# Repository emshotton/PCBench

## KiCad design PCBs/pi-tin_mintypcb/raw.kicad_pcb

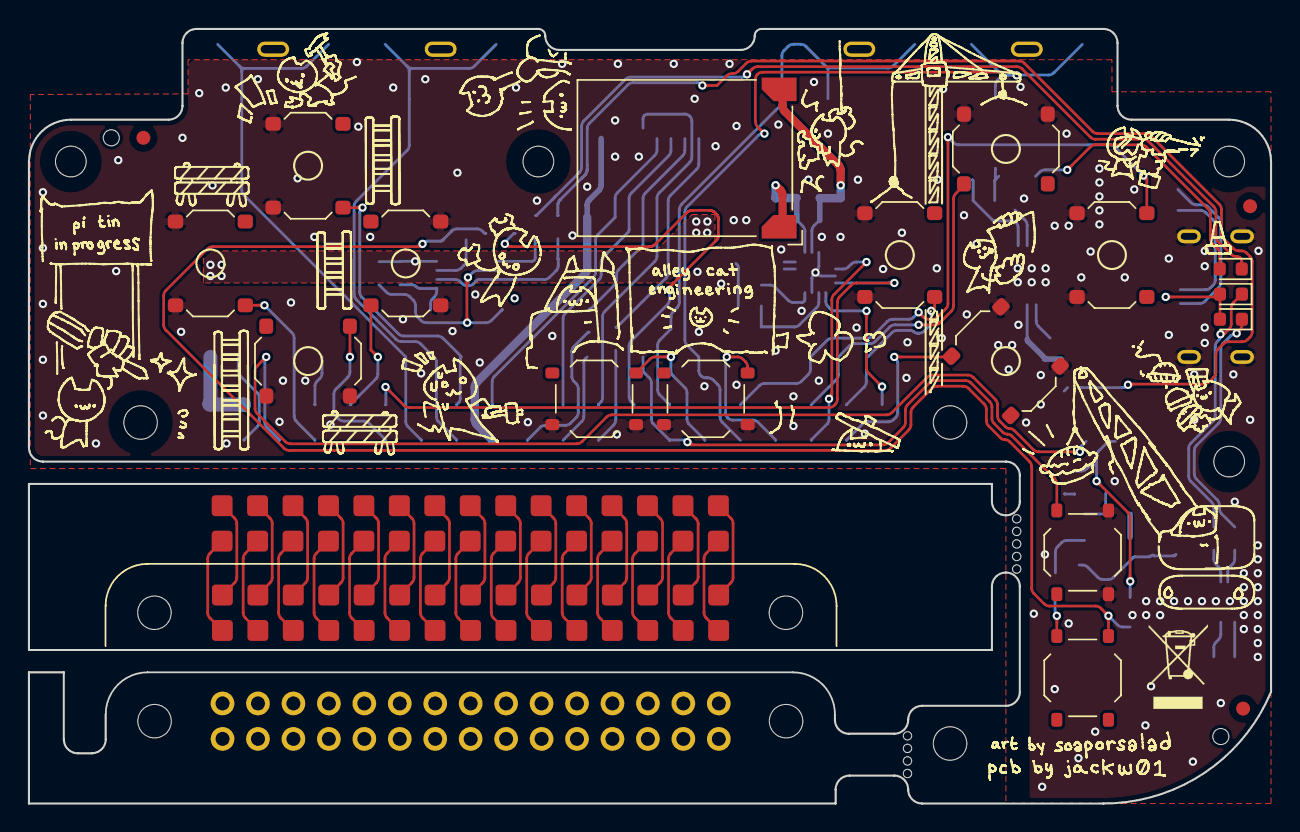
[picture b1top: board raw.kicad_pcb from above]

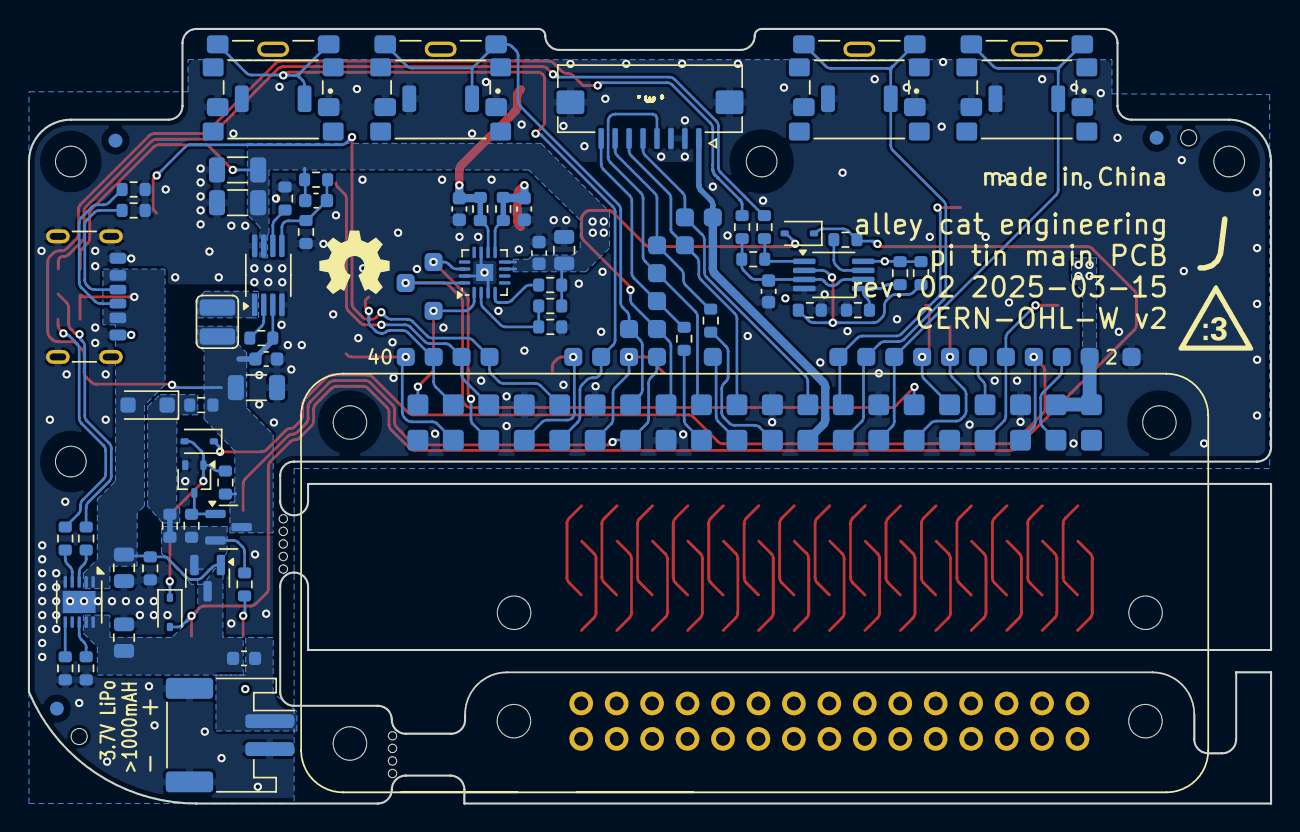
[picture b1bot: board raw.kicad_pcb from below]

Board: 2 copper layers, 89.0 x 55.5 mm, 126 parts (99 on the bottom side), 97 nets.

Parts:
A101: Raspberry Pi Zero 2 W; RASPBERRYPI-ZERO_RPI-ZERO_pi_tin
C101, C102, C105: 22u; C_1206_3216Metric
C103, C104, C108: 10u; C_0805_2012Metric
C106, C109, C112: 0.1u; C_0603_1608Metric
C107: ?; C_0603_1608Metric
C110, C111: 220p; C_0603_1608Metric
D101: DSK110; D_SOD-123F
D102: orange; LED_0603_1608Metric
D103: LED; LED_0603_1608Metric
D104: green; LED_0603_1608Metric
D105, D106, D107: BAT54; D_SOD-323
F101: 1A; Fuse_0603_1608Metric
FB103, FB104: 120R@100MHz; R_0603_1608Metric_Bridged
FID101, FID102, FID103, FID104, FID105, FID106: Fiducial_1mm_Mask2mm
H101, H103, H105, H106: MountingHole; MountingHole_2.2mm_M2_Mask_tight
H102, H104: ToolingHole; JLC_tooling_hole
J101: USB C 6 pin; USB_C_Receptacle_6PIN_generic
J102: S2B-PH-SM4-TB; JST_PH_S2B-PH-SM4-TB_1x02-1MP_P2.00mm_Horizontal
J103: FPC09-Q1.0-8; XYECONN_FPC09-Q1.0-8AH2.0
J106: Conn_02x15_Odd_Even; pi_tin_pi_simulator
J107: Conn_02x15_Odd_Even; pi_tin_pi_simulator_lands
J108: Conn_02x15_Odd_Even; pi_tin_pi_simulator_tp
L101: 2.2u; L_3225DFN
LS101: CMS-151125-076S-67; Speaker_CUI_CMR-1206S-67
Q101, Q102: 3415; SOT-23
Q103: BSS138; SOT-323_SC-70
R101, R111, R121: 10k; R_0603_1608Metric
R102: 0; R_0603_1608Metric_Bridged
R103: 0; R_0603_1608Metric
R104, R128: 22; R_0603_1608Metric
R105, R109, R110, R114, R120: 1.69k; R_0603_1608Metric
R106, R112, R113, R115, R122, R125, R127, R129: 100k; R_0603_1608Metric
R107: 49.9k; R_0603_1608Metric
R108, R126: 750k; R_0603_1608Metric
R116, R117, R123, R124: 5.1k; R_0603_1608Metric
R118: ?; R_0603_1608Metric
R119: 68k; R_0603_1608Metric
SW101, SW103, SW105, SW115: SKQGABE010; SW_PTS526
SW102, SW104, SW106, SW108, SW110, SW112, SW114, SW116: SKRRAAE010; SW_SKRR
SW107, SW109, SW111, SW113: see note 1; SW_TL3336AF160Q_or_PTS645_paste1
TP101, TP102, TP103, TP104, TP105, TP106, TP107, TP108, TP109, TP110, TP111, TP112, TP113, TP114, TP115, TP116, TP117, TP118, TP119, TP120, TP121, TP122, TP123, TP124, TP125, TP126, TP127, TP128, TP129, TP130, TP131: TestPoint_Small; TestPoint_Pad_D1.5mm
U101: LMV393; MSOP-8_3x3mm_P0.65mm
U102: MCP73833T-FCI/MF; DFN-10-1EP_3x3mm_P0.5mm_EP1.58x2.35mm
U103: PAM2401SCADJ; MSOP-8_3x3mm_P0.65mm
U104: MAX98357A; TQFN-16-1EP_3x3mm_P0.5mm_EP1.23x1.23mm

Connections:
+3.3V: A101.17 (3V3[2]), J103.1, TP113.1
+5V: A101.2 (5V[1]), A101.4 (5V[2]), C101.1, C102.1, C107.1, C108.1, C109.1, D102.2 (A), R107.2, R108.1, R119.2, R125.1, R126.1, TP102.1, U101.8 (V+), U103.7 (OUT), U104.7 (VDD), U104.8 (VDD)
+BATT: C105.1, C106.1, L101.1, Q102.3 (D), R103.1, R111.2, R112.2, R123.1, U103.3 (VIN)
/A: A101.32 (GPIO12), SW110.1, TP125.1
/B: A101.37 (GPIO26), SW112.1, TP129.1
/BATT_SW_EN: D106.1 (K), D107.2 (A), Q103.1 (G), R111.1
/DOWN: A101.11 (GPIO17/GEN0), SW104.1, TP108.1
/D/C: A101.22 (GEN/6GPIO25), J103.6, TP117.1
/I2S_BCLK: A101.12 (GPIO18), TP109.1, U104.16 (BCLK)
/I2S_DIN: A101.40 (GPIO21), TP131.1, U104.1 (DIN)
/I2S_LRCLK: A101.35 (GPIO19), TP127.1, U104.14 (LRCLK)
/L1: A101.31 (GPIO6), SW107.1, TP124.1
/L2: A101.28 (ID_SC), SW111.1, TP122.1
/LEFT: A101.7 (GPIO4/GPCKL0), SW106.1, TP104.1
/LOW_BATT: R124.1, U101.7
/PS_EN: R112.1, U103.2 (EN)
/R1: A101.13 (GPIO27/GEN2), SW109.1, TP110.1
/R2: A101.15 (GPIO22/GEN3), SW113.1, TP111.1
/RIGHT: A101.10 (RXD0/GPIO15), SW108.1, TP107.1
/RST: A101.18 (GEN5/GPIO24), J103.5, TP114.1
/SELECT: A101.29 (GPIO5), SW105.1, TP123.1
/SHUTDOWN_PI: A101.26 (~CE1/~GPIO7), D105.2 (A), TP120.1
/SHUTDOWN_PS: A101.5 (GPIO3/SCL), D107.1 (K), TP103.1
/SPECIAL1: A101.27 (ID_SD), SW115.1, TP121.1
/SPI_CS: A101.24 (~CE0/GPIO8), J103.4, TP119.1
/SPI_MOSI: J103.7, R104.1, TP115.1
/SPI_SCK: J103.8, R128.1, TP118.1
/START: A101.33 (GPIO13), SW103.1, TP126.1
/UP: A101.16 (GEN4/GPIO23), SW102.1, TP112.1
/X: A101.36 (GPIO16), SW114.1, TP128.1
/Y: A101.38 (GPIO20), SW116.1, TP130.1
/_SPI_MOSI: A101.19 (GPIO10/MOSI), R104.2
/_SPI_SCK: A101.23 (GPIO11/SCLK), R128.2
GND: A101.6 (GND[8]), A101.9 (GND[1]), A101.14 (GND[4]), A101.20 (GND[5]), A101.25 (GND[2]), A101.30 (GND[6]), A101.34 (GND[7]), A101.39 (GND[3]), C101.2, C102.2, C103.2, C104.2, C105.2, C106.2, C108.2, C109.2, C110.2, C111.2, C112.2, J101.A12 (GND), J101.B12 (GND), J101.S1 (SHIELD), J102.2, J102.MP (MountPin), J103.2, J103.3, J103.MP (MountPin), Q103.2 (S), R101.1, R113.1, R115.2, R116.1, R117.1, R118.2, R120.1, R121.1, R122.1, R127.2, SW102.2, SW103.2, SW104.2, SW105.2, SW106.2, SW107.2, SW108.2, SW109.2, SW110.2, SW111.2, SW112.2, SW113.2, SW114.2, SW115.2, SW116.2, TP106.1, U101.4 (V-), U102.5 (V_{SS}), U102.11 (EP), U103.4 (AGND), U103.8 (PGND), U104.3 (GND), U104.11 (GND), U104.15 (GND), U104.17 (PAD)
unnamed: A101.3 (GPIO2/SDA), TP101.1
unnamed: A101.21 (GPIO9/MISO), TP116.1
unnamed: A101.8 (TXD0/GPIO14), TP105.1
unnamed: C110.1, FB103.2, LS101.1
unnamed: C111.1, FB104.2, LS101.2
unnamed: D101.1 (K), R102.2, R103.2
unnamed: D102.1 (K), R105.2
unnamed: D103.1 (K), R109.2
unnamed: D104.1 (K), R110.2
unnamed: D105.1 (K), D106.2 (A), R124.2, SW101.1
unnamed: J101.A5 (CC1), R117.2
unnamed: J101.B5 (CC2), R116.2
unnamed: F101.2, J102.1
unnamed: J107.1, J108.1
unnamed: J107.2, J108.2
unnamed: J107.3, J108.3
unnamed: J107.4, J108.4
unnamed: J107.5, J108.5
unnamed: J107.6, J108.6
unnamed: J107.7, J108.7
unnamed: J107.8, J108.8
unnamed: J107.9, J108.9
unnamed: J107.10, J108.10
unnamed: J107.11, J108.11
unnamed: J107.12, J108.12
unnamed: J107.13, J108.13
unnamed: J107.14, J108.14
unnamed: J107.15, J108.15
unnamed: J107.16, J108.16
unnamed: J107.17, J108.17
unnamed: J107.18, J108.18
unnamed: J107.19, J108.19
unnamed: J107.20, J108.20
unnamed: J107.21, J108.21
unnamed: J107.22, J108.22
unnamed: J107.23, J108.23
unnamed: J107.24, J108.24
unnamed: J107.25, J108.25
unnamed: J107.26, J108.26
unnamed: J107.27, J108.27
unnamed: J107.28, J108.28
unnamed: J107.29, J108.29
unnamed: J107.30, J108.30
unnamed: C104.1, F101.1, Q101.3 (D), U102.9 (V_{BAT}), U102.10 (V_{BAT})
unnamed: Q101.2 (S), Q102.2 (S), R102.1, R106.2, R114.2
unnamed: Q102.1 (G), Q103.3 (D), R106.1
unnamed: R105.1, R129.2, U101.1
unnamed: R114.1, SW101.2
unnamed: C112.1, R123.2, R129.1, U101.3 (+), U101.6 (-)
unnamed: R107.1, R113.2, U101.2 (-)
unnamed: R119.1, R122.2, U101.5 (+)
unnamed: R120.2, U102.6 (PROG)
unnamed: R110.1, U102.3 (STAT1)
unnamed: R109.1, U102.4 (STAT2)
unnamed: R121.2, U102.8 (THERM)
unnamed: C107.2, R108.2, R115.1, U103.5 (FB)
unnamed: L101.2, U103.1 (LX)
unnamed: R118.1, U103.6 (RSET)
unnamed: R125.2, R127.1, U104.2 (GAIN_SLOT)
unnamed: FB104.1, U104.10 (OUTN)
unnamed: FB103.1, U104.9 (OUTP)
unnamed: R126.2, U104.4 (~SD_MODE)
VBUS: C103.1, D101.2 (A), D103.2 (A), D104.2 (A), J101.A9 (VBUS), J101.B9 (VBUS), Q101.1 (G), R101.2, U102.1 (V_{DD}), U102.2 (V_{DD})

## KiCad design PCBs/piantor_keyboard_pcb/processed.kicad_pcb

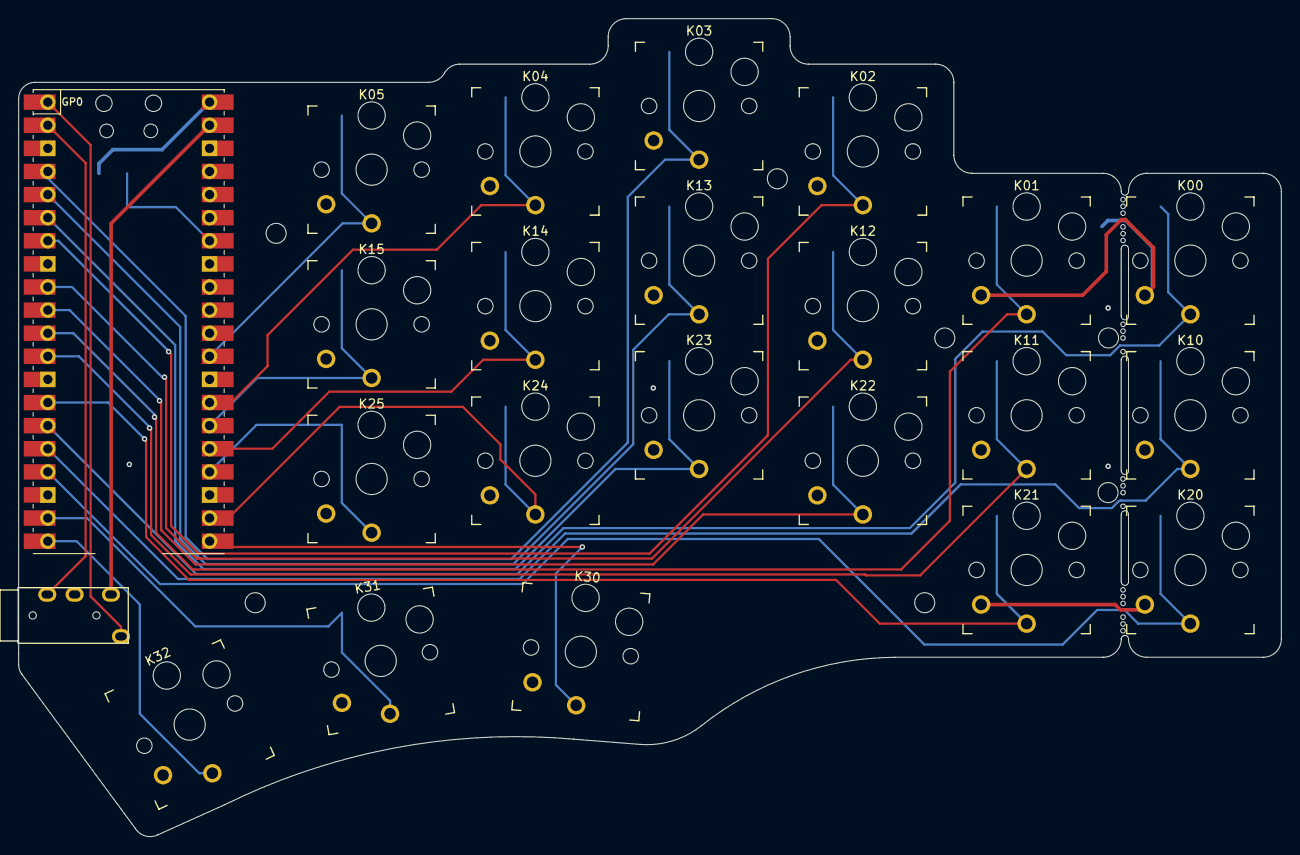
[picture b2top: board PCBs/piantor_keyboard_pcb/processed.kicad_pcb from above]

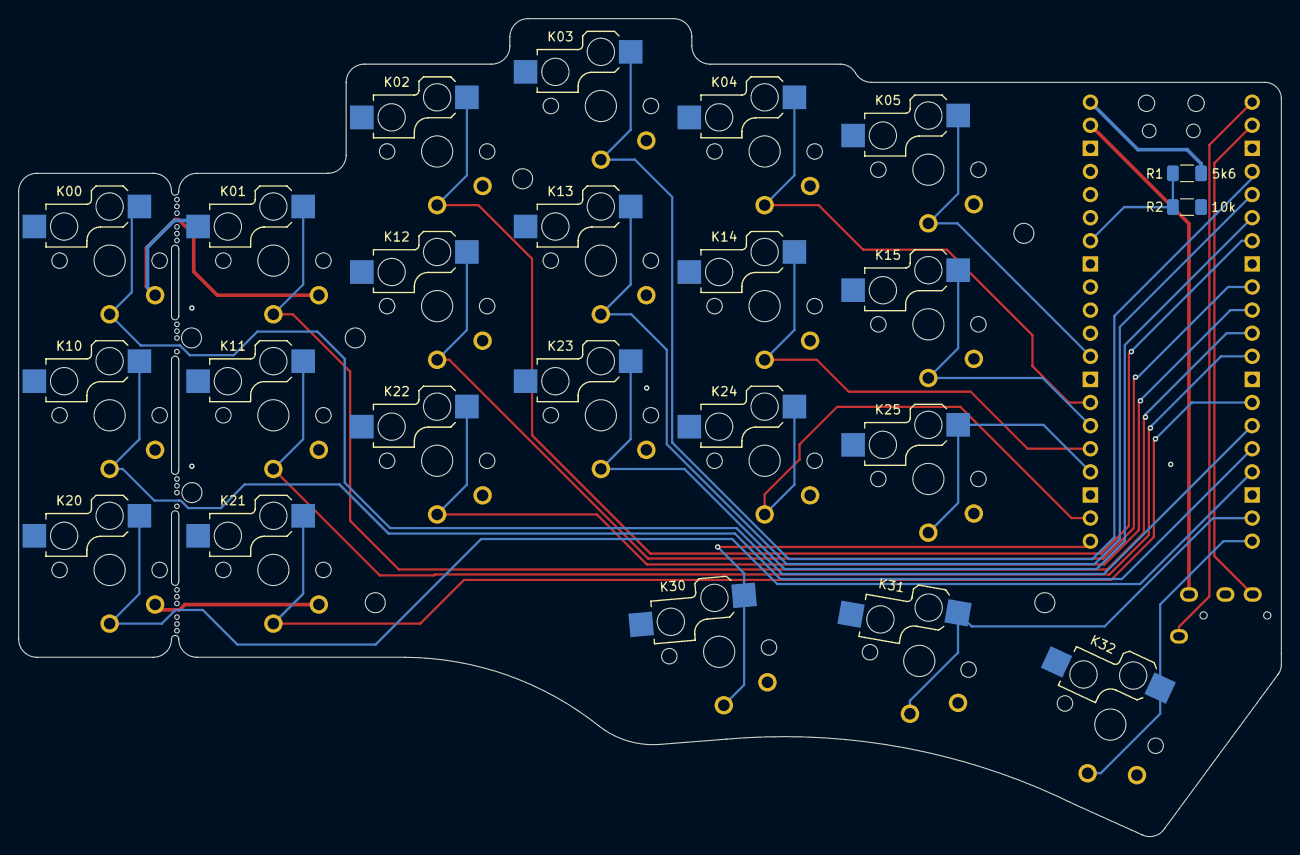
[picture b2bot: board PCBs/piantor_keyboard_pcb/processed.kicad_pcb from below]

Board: 2 copper layers, 138.8 x 89.9 mm, 36 parts (13 on the bottom side), 27 nets.

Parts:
H1, H1#2, H2, H3, H4, H4#2, H4#3: MountingHole; MountingHole_2.2mm_M2-8mm
J1: TRRS; TRRS-PJ-320A
K00, K01, K02, K03, K04, K05, K10, K11, K12, K13, K14, K15, K20, K21, K22, K23, K24, K25, K30, K31, K32: KEYSW; Kailh_socket_PG1350_optional
MB1, MB2: MountingHole; mousebites_2
MB3, MB4: MountingHole; mousebites_3
R1: 5k6; R_1206_3216Metric_Pad1.30x1.75mm_HandSolder
R2: 10k; R_1206_3216Metric_Pad1.30x1.75mm_HandSolder
U2: Pico; RPi_Pico_SMD_TH

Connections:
/k00: K00.1, U2.15 (GPIO11)
/k01: K01.1, U2.11 (GPIO8)
/k02: K02.1, U2.7 (GPIO5)
/k03: K03.1, U2.4 (GPIO2)
/k04: K04.1, U2.27 (GPIO21)
/k05: K05.1, U2.29 (GPIO22)
/k10: K10.1, U2.16 (GPIO12)
/k11: K11.1, U2.12 (GPIO9)
/k12: K12.1, U2.9 (GPIO6)
/k13: K13.1, U2.5 (GPIO3)
/k14: K14.1, U2.25 (GPIO19)
/k15: K15.1, U2.26 (GPIO20)
/k20: K20.1, U2.17 (GPIO13)
/k21: K21.1, U2.14 (GPIO10)
/k22: K22.1, U2.10 (GPIO7)
/k23: K23.1, U2.6 (GPIO4)
/k24: K24.1, U2.22 (GPIO17)
/k25: K25.1, U2.24 (GPIO18)
/k30: K30.1, U2.21 (GPIO16)
/k31: K31.1, U2.19 (GPIO14)
/k32: K32.1, U2.20 (GPIO15)
GND: J1.3 (RING1), K00.2, K01.2, K02.2, K03.2, K04.2, K05.2, K10.2, K11.2, K12.2, K13.2, K14.2, K15.2, K20.2, K21.2, K22.2, K23.2, K24.2, K25.2, K30.2, K31.2, K32.2, R2.2, U2.3 (GND), U2.8 (GND), U2.13 (GND), U2.18 (GND), U2.23 (GND), U2.28 (GND), U2.33 (AGND), U2.38 (GND)
VBUS: R1.1, U2.40 (VBUS)
VCC: J1.2 (TIP), U2.39 (VSYS)
rx: J1.4 (RING2), U2.2 (GPIO1)
tx: J1.1 (SLEEVE), U2.1 (GPIO0)
vbus_sense: R1.2, R2.1, U2.34 (GPIO28_ADC2)

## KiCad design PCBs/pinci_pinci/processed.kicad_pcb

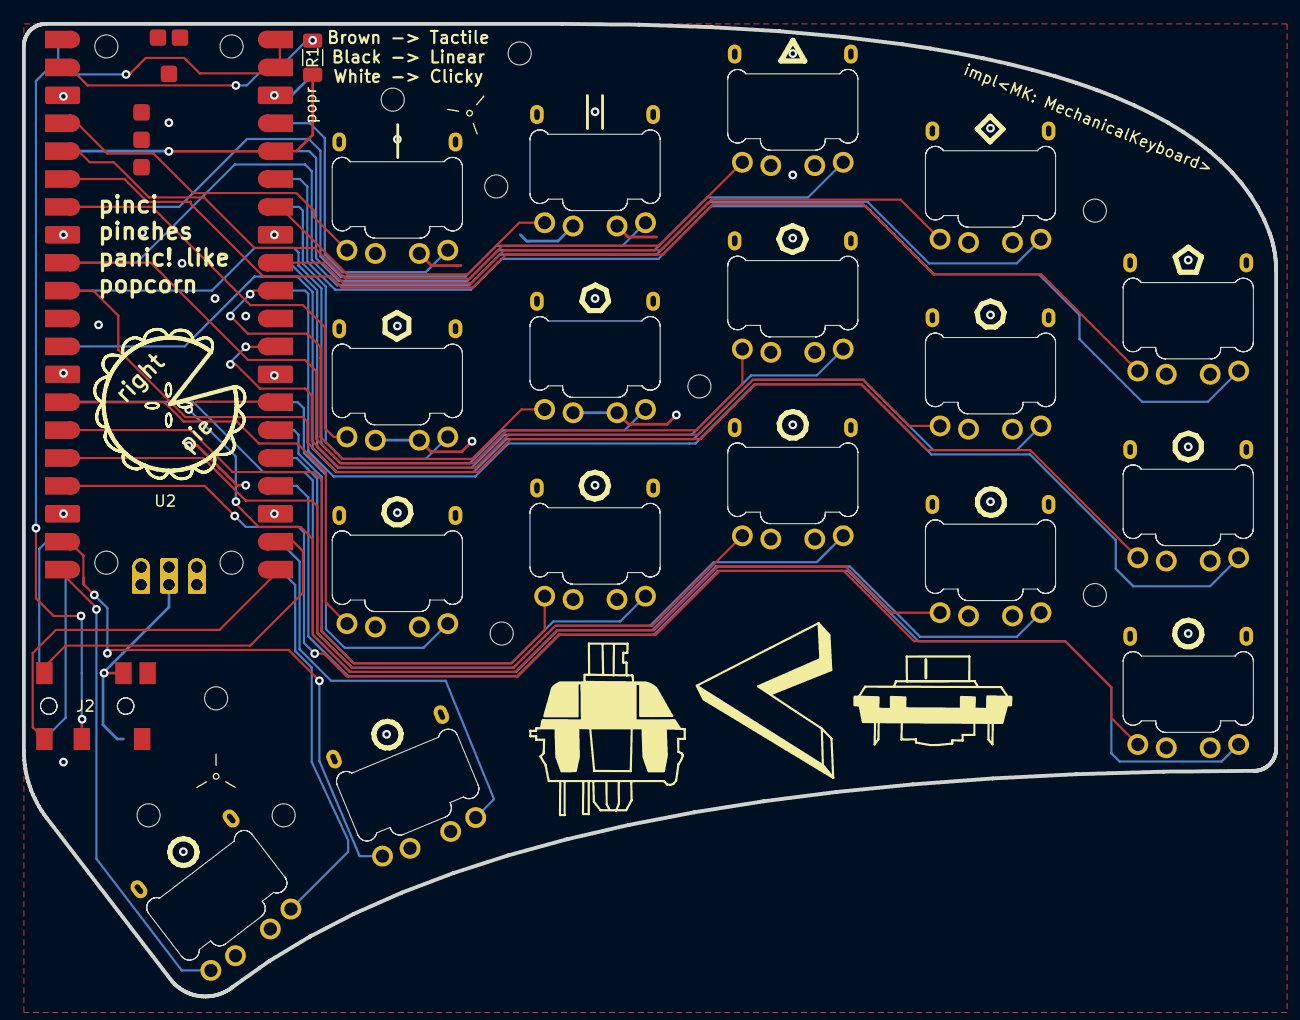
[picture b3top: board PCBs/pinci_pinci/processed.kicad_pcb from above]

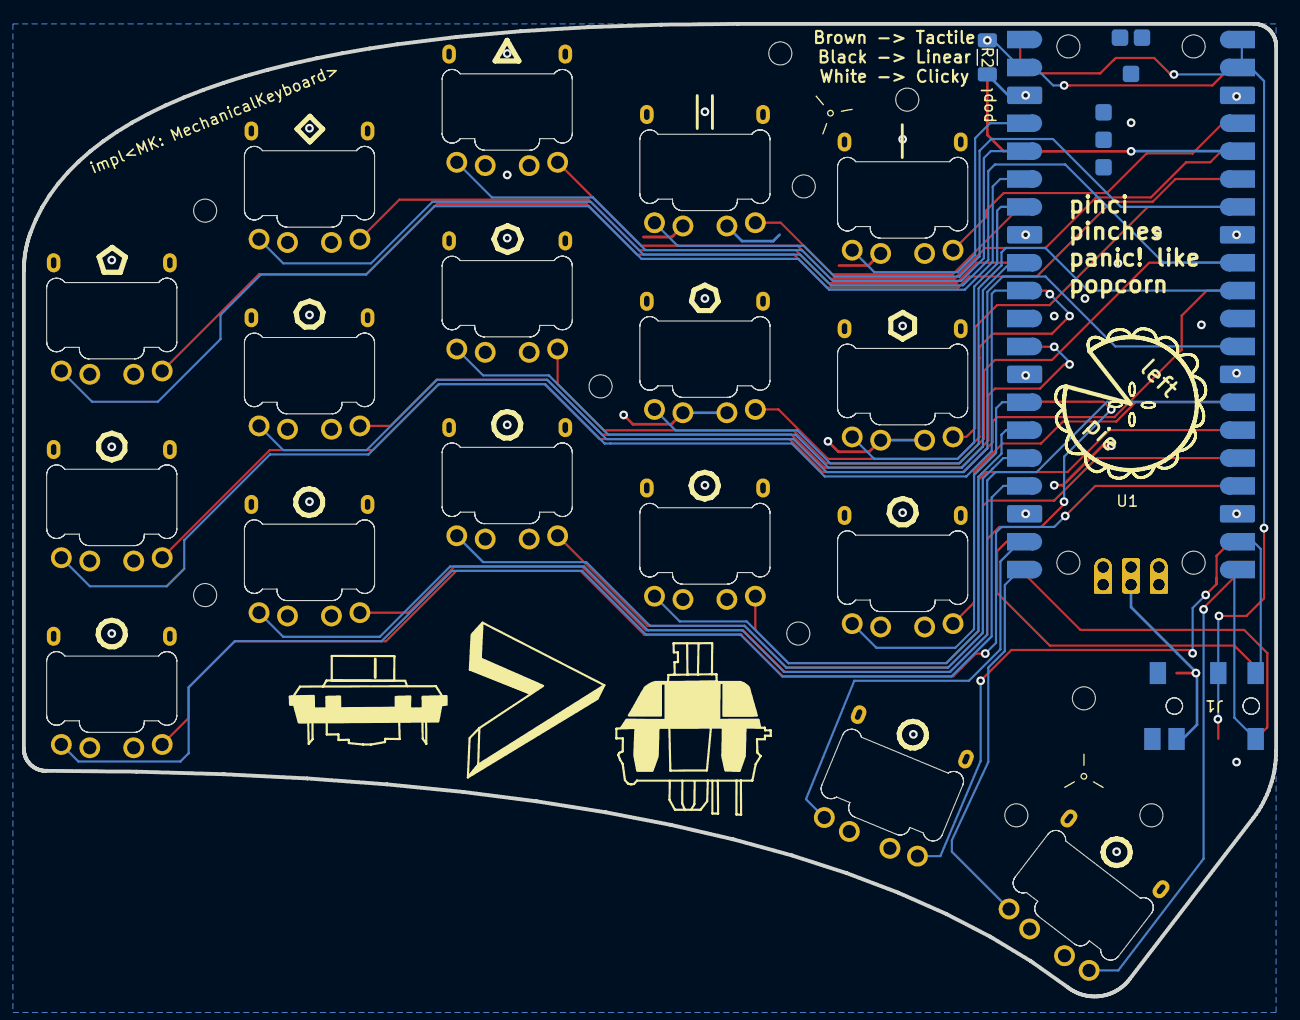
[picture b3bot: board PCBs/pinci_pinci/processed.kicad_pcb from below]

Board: 2 copper layers, 114.0 x 88.5 mm, 29 parts (5 on the bottom side), 42 nets.

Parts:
H1, H2: MountingHole; 90611A112_Screw_Mount_Nut
H3, H4, H5, H6: MountingHole; M2_Hole
J1, J2: AudioJack4; TRRS_Socket_54-00177
R1, R2: 10k; R_1206_3216Metric_Pad1.30x1.75mm_HandSolder
SW1, SW2, SW3, SW4, SW5, SW6, SW7, SW8, SW9, SW10, SW11, SW12, SW13, SW14, SW15, SW16, SW17: SW_Push_Dual; Kailh_PG1232
U1, U2: PICO; raspberrypi_pico

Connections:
+3V3: R1.2, U1.36 (3V3), U2.36 (3V3)
GND: J1.T, J2.T, R2.1, SW1.2, SW1.4, SW2.2, SW2.4, SW3.2, SW3.4, SW4.2, SW4.4, SW5.2, SW5.4, SW6.2, SW6.4, SW7.2, SW7.4, SW8.2, SW8.4, SW9.2, SW9.4, SW10.2, SW10.4, SW11.2, SW11.4, SW12.2, SW12.4, SW13.2, SW13.4, SW14.2, SW14.4, SW15.2, SW15.4, SW16.2, SW16.4, SW17.2, SW17.4, U1.3 (GND), U1.8 (GND), U1.13 (GND), U1.18 (GND), U1.23 (GND), U1.28 (GND), U1.33 (AGND), U1.38 (GND), U1.D2 (GND), U2.3 (GND), U2.8 (GND), U2.13 (GND), U2.18 (GND), U2.23 (GND), U2.28 (GND), U2.33 (AGND), U2.38 (GND), U2.D2 (GND)
L1: SW1.3, U1.4 (GP2)
L2: SW2.3, U1.34 (GP28)
L3: SW3.3, U1.5 (GP3)
L4: SW4.3, U1.32 (GP27)
L5: SW5.3, U1.6 (GP4)
L6: SW6.3, U1.7 (GP5)
L7: SW7.3, U1.31 (GP26)
L8: SW8.3, U1.9 (GP6)
L9: SW9.3, U1.29 (GP22)
L10: SW10.3, U1.10 (GP7)
L11: SW11.3, U1.14 (GP10)
L12: SW12.3, U1.15 (GP11)
L13: SW13.3, U1.16 (GP12)
L14: SW14.3, U1.27 (GP21)
L15: SW15.3, U1.17 (GP13)
L16: SW16.3, U1.20 (GP15)
L17: SW17.3, U1.19 (GP14)
LR_ID: R1.1, R2.2, U1.2 (GP1), U2.2 (GP1)
L_RX: J1.S, U1.22 (GP17)
L_TX: J1.R2, U1.21 (GP16)
R1: SW1.1, U2.4 (GP2)
R2: SW2.1, U2.34 (GP28)
R3: SW3.1, U2.5 (GP3)
R4: SW4.1, U2.32 (GP27)
R5: SW5.1, U2.6 (GP4)
R6: SW6.1, U2.7 (GP5)
R7: SW7.1, U2.31 (GP26)
R8: SW8.1, U2.9 (GP6)
R9: SW9.1, U2.29 (GP22)
R10: SW10.1, U2.10 (GP7)
R11: SW11.1, U2.14 (GP10)
R12: SW12.1, U2.15 (GP11)
R13: SW13.1, U2.16 (GP12)
R14: SW14.1, U2.27 (GP21)
R15: SW15.1, U2.17 (GP13)
R16: SW16.1, U2.20 (GP15)
R17: SW17.1, U2.19 (GP14)
R_RX: J2.R2, U2.22 (GP17)
R_TX: J2.S, U2.21 (GP16)
VBUS: J1.R1, J2.R1, U1.39 (VSYS), U1.40 (VBUS), U2.39 (VSYS), U2.40 (VBUS)

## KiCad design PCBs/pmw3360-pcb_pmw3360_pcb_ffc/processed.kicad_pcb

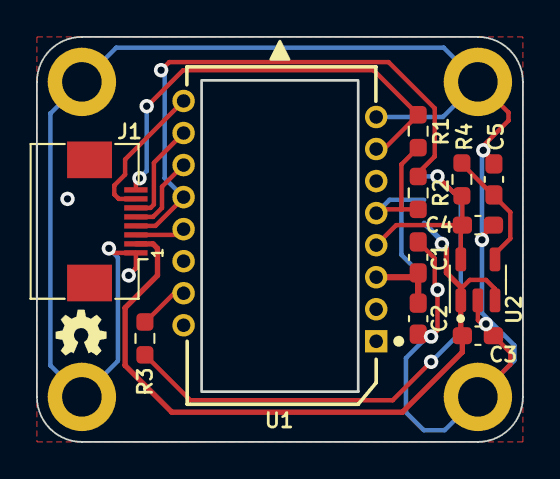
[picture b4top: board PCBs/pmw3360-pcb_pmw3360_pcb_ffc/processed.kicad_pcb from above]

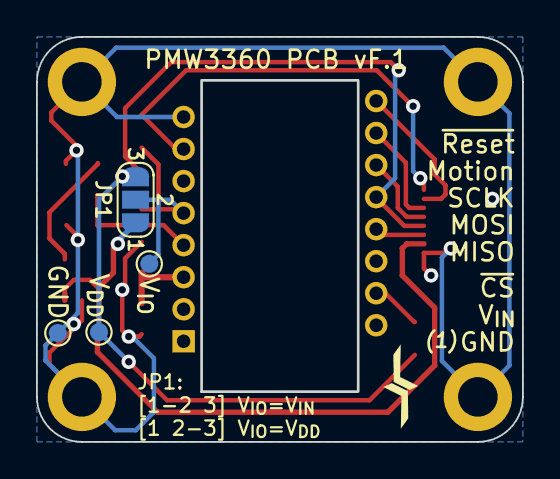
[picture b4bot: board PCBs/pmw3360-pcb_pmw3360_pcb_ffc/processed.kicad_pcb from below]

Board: 2 copper layers, 27.0 x 22.5 mm, 20 parts (4 on the bottom side), 13 nets.

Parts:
C1: 4.7uF/10V; C_0603_1608Metric_Pad1.08x0.95mm_HandSolder
C2: 100nF; C_0603_1608Metric_Pad1.08x0.95mm_HandSolder
C3, C4: 1uF; C_0603_1608Metric_Pad1.08x0.95mm_HandSolder
C5: 22nF; C_0603_1608Metric_Pad1.08x0.95mm_HandSolder
H1, H2, H3, H4: MountingHole_Pad; MountingHole_2.2mm_M2_ISO14580_Pad
J1: Interface; FPC_8P_0.5mm_AFC01-S08FCA-00
JP1: SolderJumper_3_Open; SolderJumper-3_P1.3mm_Open_RoundedPad1.0x1.5mm_NumberLabels
R1, R2: 10k; R_0603_1608Metric_Pad0.98x0.95mm_HandSolder
R3: 39R; R_0603_1608Metric_Pad0.98x0.95mm_HandSolder
R4: 28k; R_0603_1608Metric_Pad0.98x0.95mm_HandSolder
TP1: V_{IO}; TestPoint_Pad_D1.0mm
TP2: V_{DD}; TestPoint_Pad_D1.0mm
TP3: GND; TestPoint_Pad_D1.0mm
U1: PMW3360; PMW3360DM-T2QU 16Pin
U2: TLV74318PDBVR; SOT-23-5

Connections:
/CS: J1.3, U1.13 (~CS)
/MISO: J1.4, R2.2, U1.12 (MISO)
/MOSI: J1.5, U1.11 (MOSI)
/MOTION: J1.7, U1.9 (MOTION)
/RESET: J1.8, R1.2, U1.7 (~RESET)
/SCLK: J1.6, U1.10 (SCLK)
GND: C1.2, C2.2, C3.2, C4.2, C5.2, H1.1, H2.1, H3.1, H4.1, J1.1, TP3.1, U1.8 (GND), U2.2 (GND)
unnamed: R3.2, U1.15 (LED_P)
unnamed: C1.1, C2.1, U1.3 (VDDPIX)
unnamed: C5.1, R4.2, U2.4 (NC)
VDD: C4.1, JP1.3 (B), R3.1, R4.1, TP2.1, U1.4 (VDD), U2.5 (OUT)
V_{IN}: C3.1, J1.2, JP1.1 (A), U2.1 (IN), U2.3 (EN)
V_{IO}: JP1.2 (C), R1.1, R2.1, TP1.1, U1.5 (VDDIO)

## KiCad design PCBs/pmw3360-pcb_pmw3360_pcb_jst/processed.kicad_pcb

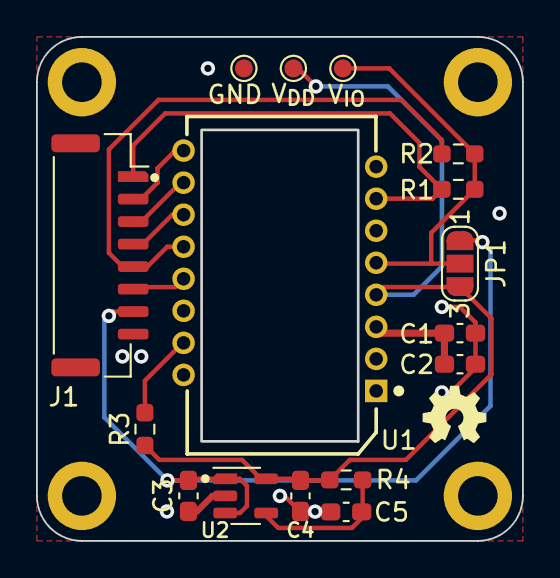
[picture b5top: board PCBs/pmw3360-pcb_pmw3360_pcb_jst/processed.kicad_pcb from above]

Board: 2 copper layers, 27.0 x 28.0 mm, 20 parts (0 on the bottom side), 13 nets.

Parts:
C1: 4.7uF/10V; C_0603_1608Metric_Pad1.08x0.95mm_HandSolder
C2: 100nF; C_0603_1608Metric_Pad1.08x0.95mm_HandSolder
C3: 1uF; C_0603_1608Metric_Pad1.08x0.95mm_HandSolder
C4: 4.7uF; C_0603_1608Metric_Pad1.08x0.95mm_HandSolder
C5: 22nF; C_0603_1608Metric_Pad1.08x0.95mm_HandSolder
H1, H2, H3, H4: MountingHole_Pad; MountingHole_2.2mm_M2_ISO14580_Pad
J1: Conn_01x08; JST_GH_SM08B-GHS-TB_1x08-1MP_P1.25mm_Horizontal
JP1: SolderJumper_3_Open; SolderJumper-3_P1.3mm_Open_RoundedPad1.0x1.5mm_NumberLabels
R1, R2: 10k; R_0603_1608Metric_Pad0.98x0.95mm_HandSolder
R3: 39R; R_0603_1608Metric_Pad0.98x0.95mm_HandSolder
R4: 28k; R_0603_1608Metric_Pad0.98x0.95mm_HandSolder
TP1: V_{IO}; TestPoint_Pad_D1.0mm
TP2: V_{DD}; TestPoint_Pad_D1.0mm
TP3: GND; TestPoint_Pad_D1.0mm
U1: PMW3360DM-T2QU; PMW3360DM-T2QU 16Pin
U2: TLV74318PDBVR; SOT-23-5

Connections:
/CS: J1.6, U1.13 (~CS)
/MISO: J1.5, R2.2, U1.12 (MISO)
/MOSI: J1.4, U1.11 (MOSI)
/MOTION: J1.2, U1.9 (MOTION)
/RESET: J1.1, R1.2, U1.7 (~RESET)
/SCLK: J1.3, U1.10 (SCLK)
GND: C1.2, C2.2, C3.2, C4.2, C5.2, H1.1, H2.1, H3.1, H4.1, J1.8, TP3.1, U1.8 (GND), U2.2 (GND)
unnamed: R3.2, U1.15 (LED_P)
unnamed: C1.1, C2.1, U1.3 (VDDPIX)
unnamed: C5.1, R4.2, U2.4 (NC)
VDD: C4.1, JP1.3 (B), R3.1, R4.1, TP2.1, U1.4 (VDD), U2.5 (OUT)
V_{IN}: C3.1, J1.7, JP1.1 (A), U2.1 (IN), U2.3 (EN)
V_{IO}: JP1.2 (C), R1.1, R2.1, TP1.1, U1.5 (VDDIO)

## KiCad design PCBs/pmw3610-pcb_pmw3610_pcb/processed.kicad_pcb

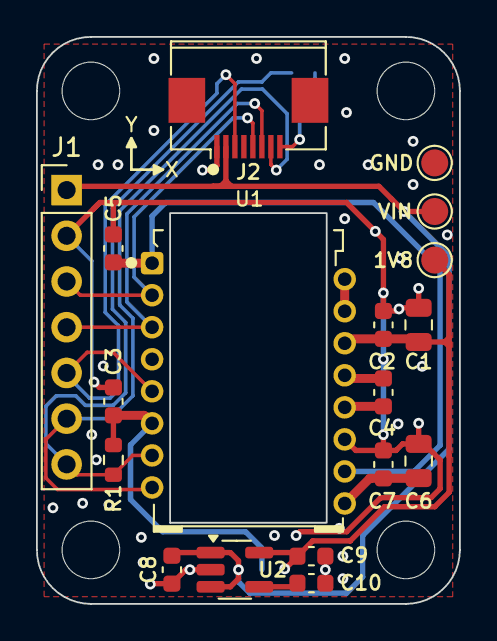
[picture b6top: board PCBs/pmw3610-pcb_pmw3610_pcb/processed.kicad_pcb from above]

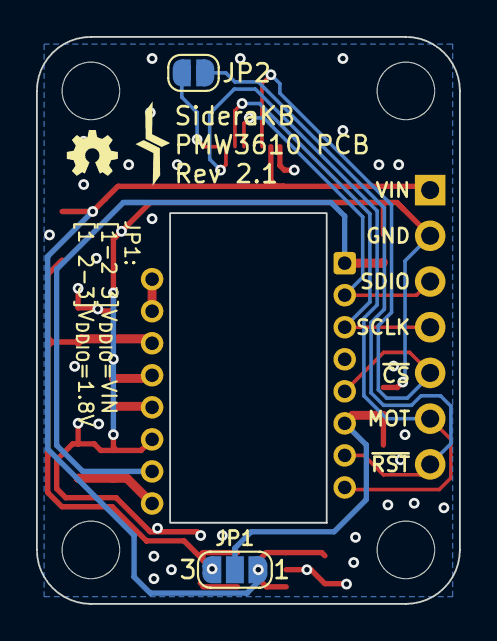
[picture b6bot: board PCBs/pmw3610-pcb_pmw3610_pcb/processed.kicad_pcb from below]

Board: 2 copper layers, 23.5 x 31.5 mm, 24 parts (6 on the bottom side), 16 nets.

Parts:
C1: 3.3uF/16V; C_0805_2012Metric
C2, C3, C4: 100nF; C_0603_1608Metric
C5, C7: 10nF; C_0603_1608Metric
C6: 10uF; C_0805_2012Metric
C8, C9: 1uF; C_0603_1608Metric
C10: 22nF; C_0603_1608Metric
H1, H2, H3, H4: MountingHole; MountingHole_3.2mm_M3_ISO14580
J1: Conn_PinHeader; PinHeader_1x07_P2.54mm_Vertical
J2: Conn_FPC; FPC_8P_0.5mm_AFC01-S08FCA-00
JP1: SolderJumper_3_Open; SolderJumper-3_P1.3mm_Open_RoundedPad1.0x1.5mm_NumberLabels
JP2: FPC_RST; SolderJumper-2_P1.3mm_Open_RoundedPad1.0x1.5mm
R1: 10k; R_0603_1608Metric
TP1, TP2, TP3: TestPoint; TestPoint_Pad_D1.5mm
U1: PMW3610; PMW3610DM-SUDU 16Pin
U2: TLV74318PDBVR; SOT-23-5_HandSoldering

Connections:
+1V8: C1.1, C2.1, C9.1, JP1.3 (B), TP3.1, U1.14 (VDD), U2.5 (OUT)
GND: C1.2, C2.2, C3.2, C5.2, C6.2, C7.2, C8.2, C9.2, C10.2, J1.2, J2.1, TP1.1, U1.11 (GND), U2.2 (GND)
MOTION: J1.6, J2.7, U1.8 (MOTION)
unnamed: J2.8, JP2.2 (B)
unnamed: C5.1, U1.1 (+VCSEL), U1.10 (PASS_T)
unnamed: U1.15 (XYLASER), U1.16 (-VCSEL)
unnamed: C4.2, U1.13 (CN)
unnamed: C4.1, U1.12 (CP)
unnamed: C6.1, C7.1, U1.9 (VCP)
unnamed: C10.1, U2.4 (NC)
SCLK: J1.4, J2.6, U1.3 (SCLK)
SDIO: J1.3, J2.5, U1.2 (SDIO)
VDDIO: C3.1, JP1.2 (C), R1.1, U1.6 (VDDIO)
VIN: C8.1, J1.1, J2.2, JP1.1 (A), TP2.1, U2.1 (IN), U2.3 (EN)
nCS: J1.5, J2.3, U1.5 (NCS)
nRESET: J1.7, JP2.1 (A), R1.2, U1.7 (NRESET)

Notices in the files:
PCBs/pi-tin_mintypcb/raw.kicad_pcb:
CERN-OHL-W v2
Released under the CERN-OHL-W V2 license
PCBs/pmw3360-pcb_pmw3360_pcb_ffc/processed.kicad_pcb:
Open Source Hardware, CERN-OHL-P v2
